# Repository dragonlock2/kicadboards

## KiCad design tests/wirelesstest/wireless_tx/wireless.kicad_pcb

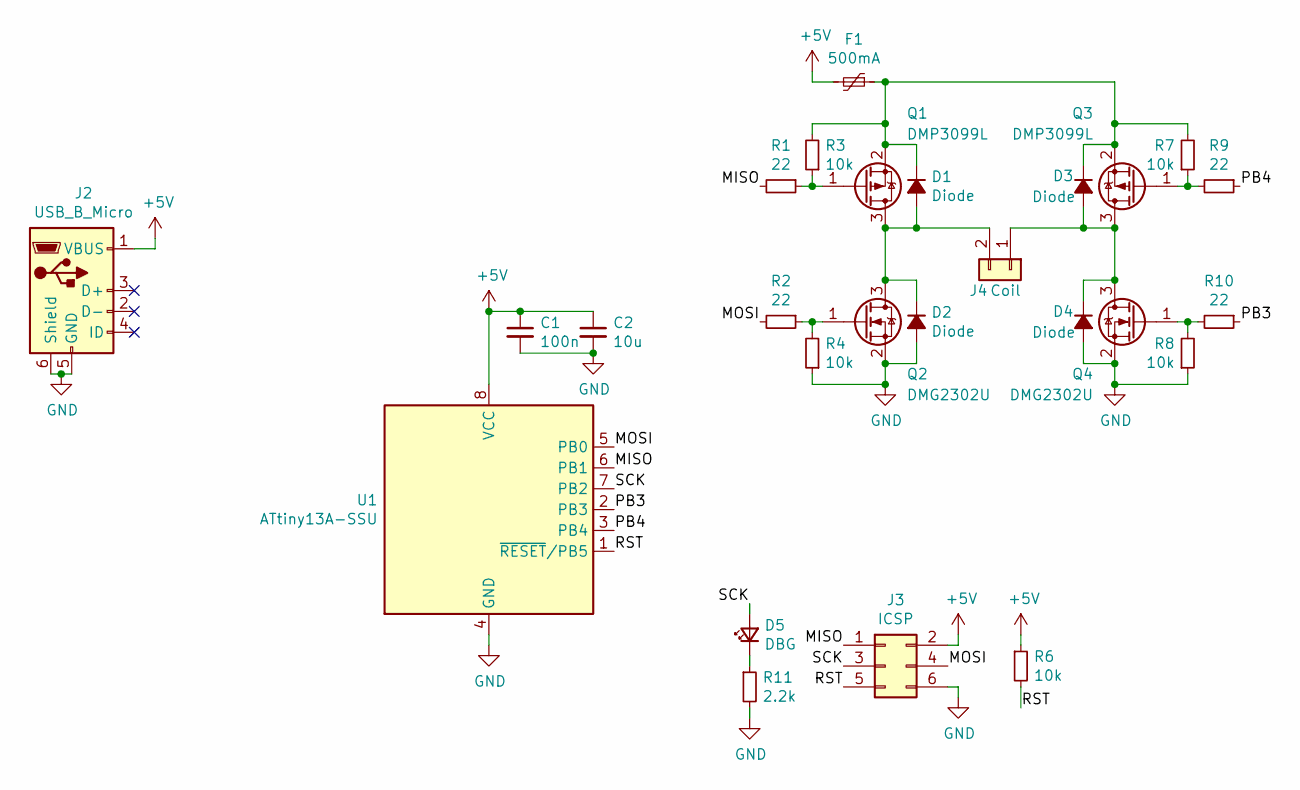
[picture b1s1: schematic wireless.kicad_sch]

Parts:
C1: 100n; C_0603_1608Metric
C2: 10u; C_0805_2012Metric
D1, D2, D3, D4: Diode; D_SMA
D5: DBG; LED_0603_1608Metric
F1: 500mA; Fuse_1206_3216Metric
J2: USB_B_Micro; USB_Micro-B_Amphenol_10103594-0001LF_Horizontal
J3: ICSP; Tag-Connect_TC2030-IDC-NL_2x03_P1.27mm_Vertical
J4: Coil; PinHeader_1x02_P2.54mm_Vertical
Q1, Q3: DMP3099L; SOT-23
Q2, Q4: DMG2302U; SOT-23
R1, R2, R9, R10: 22; R_0603_1608Metric
R3, R4, R6, R7, R8: 10k; R_0603_1608Metric
R11: 2.2k; R_0603_1608Metric
U1: ATtiny13A-SSU; SOIC-8_3.9x4.9mm_P1.27mm

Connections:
+5V: C1.1, C2.1, F1.2, J2.1 (VBUS), J3.2, R6.1, U1.8 (VCC)
/MISO: J3.1, R1.2, U1.6 (PB1)
/MOSI: J3.4, R2.2, U1.5 (PB0)
/PB3: R10.1, U1.2 (PB3)
/PB4: R9.1, U1.3 (PB4)
/RST: J3.5, R6.2, U1.1 (~RESET/PB5)
/SCK: D5.2 (A), J3.3, U1.7 (PB2)
GND: C1.2, C2.2, D2.2 (A), D4.2 (A), J2.5 (GND), J2.6 (Shield), J3.6, Q2.2 (S), Q4.2 (S), R4.1, R8.1, R11.2, U1.4 (GND)
unnamed: D1.1 (K), D3.1 (K), F1.1, Q1.2 (S), Q3.2 (S), R3.2, R7.2
unnamed: D1.2 (A), D2.1 (K), J4.2, Q1.3 (D), Q2.3 (D)
unnamed: D3.2 (A), D4.1 (K), J4.1, Q3.3 (D), Q4.3 (D)
unnamed: D5.1 (K), R11.1
unnamed: Q1.1 (G), R1.1, R3.1
unnamed: Q2.1 (G), R2.1, R4.2
unnamed: Q3.1 (G), R7.1, R9.2
unnamed: Q4.1 (G), R8.2, R10.2

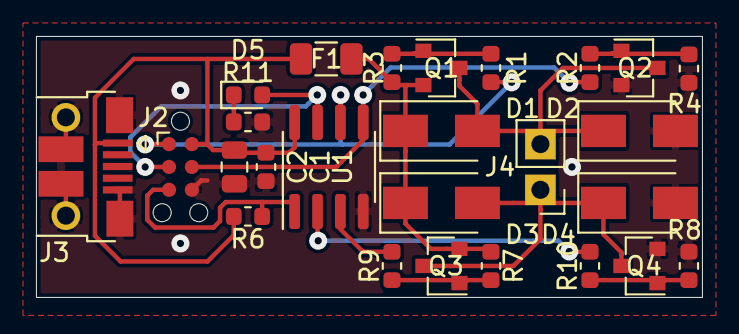
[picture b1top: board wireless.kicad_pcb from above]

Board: 2 copper layers, 37.0 x 14.5 mm, 26 parts (0 on the bottom side), 16 nets.
